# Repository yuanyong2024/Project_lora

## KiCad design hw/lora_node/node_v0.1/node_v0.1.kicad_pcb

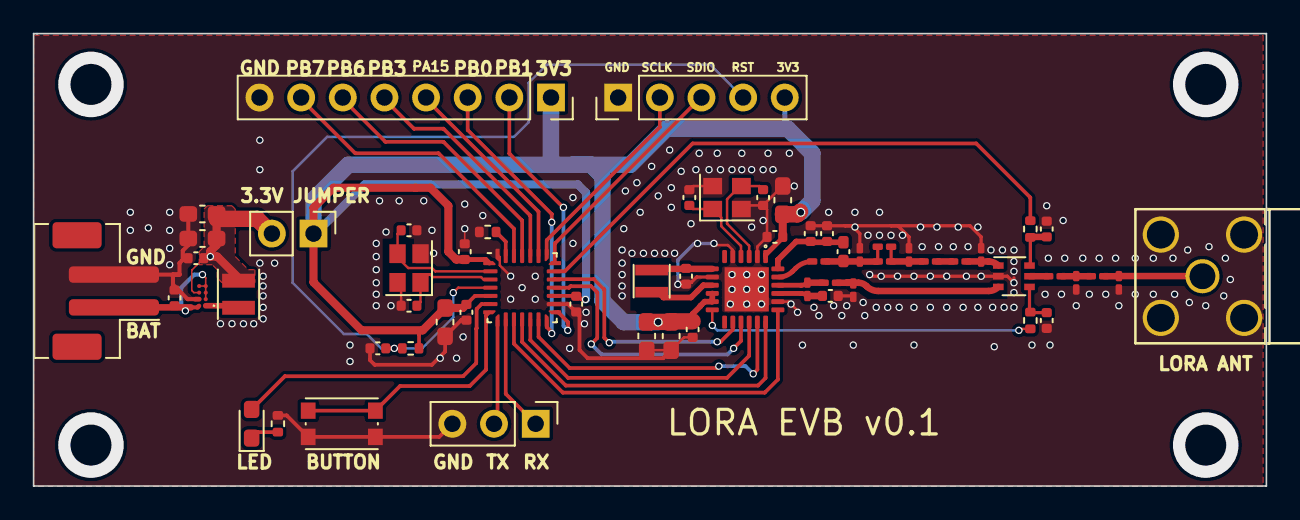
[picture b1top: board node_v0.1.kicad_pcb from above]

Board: 2 copper layers, 75.2 x 27.6 mm, 61 parts (0 on the bottom side), 48 nets.

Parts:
AE1: Antenna; CONN_142-0701-301_CIN
C1, C2, C4, C5, C13: 12pF; C_0402_1005Metric
C3, C16, C17, C24, C25, C28, C30, C31, C32, C34: 0.1uF; C_0402_1005Metric
C6, C7: TBD; C_0402_1005Metric
C8, C9, C10, C11, C12, C14, C18, C19, C20: TBD; C_0201_0603Metric_Pad0.64x0.40mm_HandSolder
C15: 12pF; C_0201_0603Metric_Pad0.64x0.40mm_HandSolder
C21: 470nF; C_0402_1005Metric
C22: 1uF; C_0603_1608Metric_Pad1.08x0.95mm_HandSolder
C23, C26, C27, C29, C33: 10uF; C_0603_1608Metric_Pad1.08x0.95mm_HandSolder
D1: LED; LED_0603_1608Metric_Pad1.05x0.95mm_HandSolder
J1: DEBUG; PinHeader_1x05_P2.54mm_Vertical
J2: UART; PinHeader_1x03_P2.54mm_Vertical
J3: Conn_01x02_Pin; JST_PH_B2B-PH-SM4-TB_1x02-1MP_P2.00mm_Vertical
J4: Spare IO; PinSocket_1x08_P2.54mm_Vertical
J5: Conn_01x02_Pin; PinHeader_1x02_P2.54mm_Vertical
L1, L3, L4, L6: TBD; L_0201_0603Metric_Pad0.64x0.40mm_HandSolder
L2: TBD; L_0402_1005Metric_Pad0.77x0.64mm_HandSolder
L5: L; L_0201_0603Metric_Pad0.64x0.40mm_HandSolder
L7: 15uH; L_Taiyo-Yuden_MD-2020
L8: 2.2uH; L_Changjiang_FNR252010S
R1, R2: 2.2K; R_0402_1005Metric
R3, R4: 100R; R_0402_1005Metric
R5: 0R; R_0402_1005Metric
SW1: SW_Push; SW_Push_1P1T_NO_CK_KMR2
U1: STM32L031G6U6; QFN-28_4x4mm_P0.5mm
U2: LLCC68
U3: SOT-363_SC-70-6
U4: TPS62743YFPR; BGA8N40P2X4_87X156X50
Y1, Y2: 32MHz; Crystal_SMD_2520-4Pin_2.5x2.0mm

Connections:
+3.3V: C22.2, C23.2, C24.2, C28.2, C29.2, C30.2, C31.2, C32.2, C33.2, J1.5, J4.1, J5.1, R2.1, U1.1 (VDD), U1.5 (VDDA), U1.17 (VDD), U2.1 (VDD_IN), U2.10 (VBAT), U2.11 (VBAT_IO)
/Lora/DIO2: R3.1, U2.12 (DIO2)
/Lora/VR_PA: C6.2, C7.2, L2.1, U2.24 (VR_PA)
/MCU/PA15: J4.4, U1.23 (PA15)
/MCU/SWCLK: J1.2, U1.22 (PA14)
/MCU/SWDIO: J1.3, U1.21 (PA13)
GND: AE1.2 (GND), C1.1, C2.1, C3.1, C4.1, C5.1, C6.1, C7.1, C9.2, C10.2, C12.2, C13.2, C15.2, C16.2, C17.2, C19.2, C20.2, C21.1, C22.1, C23.1, C24.1, C25.1, C26.1, C27.1, C28.1, C29.1, C30.1, C31.1, C32.1, C33.1, C34.1, J1.1, J2.3, J3.2, J4.8, R1.2, R5.1, SW1.2, U1.16 (VSS), U1.28 (VSS), U2.2 (GND), U2.5 (GND), U2.8 (GND), U2.20 (GND), U2.25 (PAD), U3.2 (GND), U4.B2 (GND), Y1.2, Y1.4, Y2.2, Y2.4
LORA_ANT_SW: R4.1, U1.20 (PA10)
LORA_BUSY: U1.19 (PA9), U2.14 (BUSY)
unnamed: AE1.1 (A), C19.1, L6.2
unnamed: C8.2, C9.1, L1.2, L2.2, L3.1
unnamed: C8.1, C10.1, C11.2, L3.2
unnamed: C11.1, L4.1
unnamed: C18.1, C20.1, L6.1
unnamed: D1.2 (A), U1.6 (PA0)
unnamed: D1.1 (K), R1.1
unnamed: J2.1, U1.9 (PA3)
unnamed: J2.2, U1.8 (PA2)
unnamed: C34.2, J3.1, U4.A2 (VIN), U4.B1 (EN), U4.C1 (VSEL1), U4.D1 (VSEL2), U4.D2 (VSEL3)
unnamed: J4.2, U1.15 (PB1)
unnamed: J4.3, U1.14 (PB0)
unnamed: J4.5, U1.24 (PB3)
unnamed: J4.6, U1.25 (PB6)
unnamed: J4.7, U1.26 (PB7)
unnamed: C25.2, C26.2, C27.2, J5.2, L8.2, U4.C2 (VOS)
unnamed: R5.2, U1.27 (BOOT0)
unnamed: SW1.1, U1.7 (PA1)
unnamed: C1.2, U1.2 (PC14), Y1.3
unnamed: C2.2, U1.3 (PC15), Y1.1
unnamed: L7.2, U2.9 (DCC_SW)
unnamed: C14.2, L5.1, U2.22 (RFI_N)
unnamed: C13.1, L5.2, U2.21 (RFI_P)
unnamed: L1.1, U2.23 (RFO)
unnamed: C21.2, L7.1, U2.7 (VREG)
unnamed: C4.2, U2.3 (XTA), Y2.3
unnamed: C5.2, U2.4 (XTB), Y2.1
unnamed: C16.1, R3.2, U3.4 (CTRL)
unnamed: C12.1, L4.2, U3.1 (RF1)
unnamed: C14.1, C15.1, U3.3 (RF2)
unnamed: C18.2, U3.5 (RFC)
unnamed: C17.1, R4.2, U3.6 (~CTRL)
unnamed: L8.1, U4.A1 (SW)
SPI_MISO: U1.12 (PA6), U2.16 (MISO)
SPI_MOSI: U1.13 (PA7), U2.17 (MOSI)
SPI_SCLK: U1.11 (PA5), U2.18 (SCLK)
~LORA_CS: U1.10 (PA4), U2.19 (NSS)
~LORA_RST: U1.18 (PA8), U2.15 (NRESET)
~RESET: C3.2, J1.4, R2.2, U1.4 (NRST)

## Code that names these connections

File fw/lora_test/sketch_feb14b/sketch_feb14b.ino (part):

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#include "llcc68.h"


#define LORA_BUSY     PA9
#define LORA_ANT_PWR  PA10
#define LORA_DIO1     PB1   //interrupt pin

#define LED     PA0
#define BUTTON  PA1


#define TX_MODE
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

void gpio_init(void){
  pinMode(LORA_BUSY,INPUT);
  pinMode(LORA_ANT_PWR,OUTPUT);
  pinMode(LORA_DIO1,INPUT_PULLUP);   //default status is pull-down
  pinMode(LED,OUTPUT);
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  llcc68_set_tx(nullptr,100);
  digitalWrite(LED,LOW);
  /*
  if(digitalRead(PA1)==0){
    delay(20);
    digitalWrite(PA0,true);
    if(digitalRead(PA1)==0){
      while(digitalRead(PA1)==0);
      Serial.println("send lora data out");
      static uint8_t press_counter = 0;
      press_counter +=1;
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      delay(10);
      llcc68_set_tx(nullptr,100);
      delay(100);
      digitalWrite(PA0,false);
    }
  }
  */
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      //Serial.printf("package received and the quantity is %d and the start address is %d\r\n",rx_buf_stat.pld_len_in_bytes,rx_buf_stat.buffer_start_pointer);
      llcc68_read_buffer(nullptr,rx_base_addr,data_buf,sizeof(data_buf));
      if(data_buf[0]!=0){
        //digitalWrite(PA0,true);
        for(char i=0;i<10;i++){
          Serial.print(data_buf[i]);
          Serial.print('-');
        }
        Serial.println(' ');
        //digitalWrite(PA0,false);
        for(char i=0;i<10;i++){
          data_buf[i] = 0;
        }
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  llcc68_set_rx(nullptr,LLCC68_RX_SINGLE_MODE);
  delay(1000);
  if(data_buf[0]!=0){
    digitalWrite(PA0,true);
    for(char i=0;i<10;i++){
      Serial.print(data_buf[i]);
      Serial.print('-');
    }
    Serial.println(' ');
    digitalWrite(PA0,false);
  }

#endif

#ifdef TX_MODE
  if(digitalRead(PA1)==0){
    delay(20);
    digitalWrite(PA0,true);
    if(digitalRead(PA1)==0){
      while(digitalRead(PA1)==0);
      Serial.println("send lora data out");
      llcc68_set_tx(nullptr,100);
      delay(100);
      digitalWrite(PA0,false);
    }
  }
#endif
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
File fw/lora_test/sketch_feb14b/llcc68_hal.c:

#include "llcc68_hal.h"


SPI_HandleTypeDef hspi1;



llcc68_hal_status_t llcc68_hal_init(void){

    HAL_Init();  // Initialize HAL Library
    __HAL_RCC_GPIOA_CLK_ENABLE(); // Enable GPIOA clock (assuming SPI1 on PA4-PA7)

    GPIO_InitTypeDef GPIO_InitStruct = {0};
    // Configure SPI1 SCK, MISO, MOSI pins (PA5, PA6, PA7)
    GPIO_InitStruct.Pin = GPIO_PIN_5 | GPIO_PIN_6 | GPIO_PIN_7;
    GPIO_InitStruct.Mode = GPIO_MODE_AF_PP;  // Alternate function, push-pull
    GPIO_InitStruct.Pull = GPIO_NOPULL;
    GPIO_InitStruct.Speed = GPIO_SPEED_FREQ_HIGH;
    GPIO_InitStruct.Alternate = GPIO_AF0_SPI1;  // Check if AF0 is correct for L0 series

    //config CS pin for SPI1
    HAL_GPIO_Init(GPIOA, &GPIO_InitStruct);
    GPIO_InitStruct.Pin = GPIO_PIN_4;
    GPIO_InitStruct.Mode = GPIO_MODE_OUTPUT_PP;
    HAL_GPIO_Init(GPIOA, &GPIO_InitStruct);

    //config RESET pin for LLCC68
    HAL_GPIO_Init(GPIOA, &GPIO_InitStruct);
    GPIO_InitStruct.Pin = GPIO_PIN_8;
    GPIO_InitStruct.Mode = GPIO_MODE_OUTPUT_PP;
    HAL_GPIO_Init(GPIOA, &GPIO_InitStruct);

    __HAL_RCC_SPI1_CLK_ENABLE();  // Enable SPI1 clock

    hspi1.Instance = SPI1;  // Use SPI1 peripheral
    hspi1.Init.Mode = SPI_MODE_MASTER;
    hspi1.Init.Direction = SPI_DIRECTION_2LINES;
    hspi1.Init.DataSize = SPI_DATASIZE_8BIT;
    hspi1.Init.CLKPolarity = SPI_POLARITY_LOW;
    hspi1.Init.CLKPhase = SPI_PHASE_1EDGE;
    hspi1.Init.NSS = SPI_NSS_SOFT;
    hspi1.Init.BaudRatePrescaler = SPI_BAUDRATEPRESCALER_16;
    hspi1.Init.FirstBit = SPI_FIRSTBIT_MSB;
    hspi1.Init.TIMode = SPI_TIMODE_DISABLE;
    hspi1.Init.CRCCalculation = SPI_CRCCALCULATION_DISABLE;
    hspi1.Init.CRCPolynomial = 7;

    if (HAL_SPI_Init(&hspi1) != HAL_OK) {
        // Initialization Error
        while (1);
    }
}


/**
 * Radio data transfer - write
 *
 * @remark Shall be implemented by the user
 *
 * @param [in] context          Radio implementation parameters
 * @param [in] command          Pointer to the buffer to be transmitted
 * @param [in] command_length   Buffer size to be transmitted
 * @param [in] data             Pointer to the buffer to be transmitted
 * @param [in] data_length      Buffer size to be transmitted
 *
 * @returns Operation status
 */
llcc68_hal_status_t llcc68_hal_write( const void* context, const uint8_t* command, const uint16_t command_length,
                                      const uint8_t* data, const uint16_t data_length ){
    // Transmit command
    HAL_GPIO_WritePin(GPIOA, GPIO_PIN_4, GPIO_PIN_RESET);
    if (HAL_SPI_Transmit(&hspi1, (uint8_t*)command, command_length, HAL_MAX_DELAY) != HAL_OK) {
        HAL_GPIO_WritePin(GPIOA, GPIO_PIN_4, GPIO_PIN_SET);
        return LLCC68_HAL_STATUS_ERROR;
    }

    // Transmit data (if data_length > 0)
    if (data_length > 0) {
        if (HAL_SPI_Transmit(&hspi1, (uint8_t*)data, data_length, HAL_MAX_DELAY) != HAL_OK) {
            HAL_GPIO_WritePin(GPIOA, GPIO_PIN_4, GPIO_PIN_SET);
            return LLCC68_HAL_STATUS_ERROR;
        }
    }
    HAL_GPIO_WritePin(GPIOA, GPIO_PIN_4, GPIO_PIN_SET);
    return LLCC68_HAL_STATUS_OK;
}


/**
 * Radio data transfer - read
 *
 * @remark Shall be implemented by the user
 *
 * @param [in] context          Radio implementation parameters
 * @param [in] command          Pointer to the buffer to be transmitted
 * @param [in] command_length   Buffer size to be transmitted
 * @param [in] data             Pointer to the buffer to be received
 * @param [in] data_length      Buffer size to be received
 *
 * @returns Operation status
 */
llcc68_hal_status_t llcc68_hal_read( const void* context, const uint8_t* command, const uint16_t command_length,
                                     uint8_t* data, const uint16_t data_length ){
    // Transmit command to the LLCC68
    HAL_GPIO_WritePin(GPIOA, GPIO_PIN_4, GPIO_PIN_RESET);
    if (HAL_SPI_Transmit(&hspi1, (uint8_t*)command, command_length, HAL_MAX_DELAY) != HAL_OK) {
        HAL_GPIO_WritePin(GPIOA, GPIO_PIN_4, GPIO_PIN_SET);
        return LLCC68_HAL_STATUS_ERROR;
    }

    // Receive data from LLCC68
    if (data_length > 0) {
        if (HAL_SPI_Receive(&hspi1, data, data_length, HAL_MAX_DELAY) != HAL_OK) {
            HAL_GPIO_WritePin(GPIOA, GPIO_PIN_4, GPIO_PIN_SET);
            return LLCC68_HAL_STATUS_ERROR;
        }
    }
    HAL_GPIO_WritePin(GPIOA, GPIO_PIN_4, GPIO_PIN_SET);
    return LLCC68_HAL_STATUS_OK;


}


/**
 * Reset the radio
 *
 * @remark Shall be implemented by the user
 *
 * @param [in] context Radio implementation parameters
 *
 * @returns Operation status
 */
llcc68_hal_status_t llcc68_hal_reset( const void* context ){
  HAL_GPIO_WritePin(GPIOA, GPIO_PIN_8, GPIO_PIN_RESET);
  delay(100);
  HAL_GPIO_WritePin(GPIOA, GPIO_PIN_8, GPIO_PIN_SET);
}


/**
 * Wake the radio up.
 *
 * @remark Shall be implemented by the user
 *
 * @param [in] context Radio implementation parameters
 *
 * @returns Operation status
 */
llcc68_hal_status_t llcc68_hal_wakeup( const void* context ){

}

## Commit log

2025-05-04 update this github repository
2025-05-05 add a datasheet in it
